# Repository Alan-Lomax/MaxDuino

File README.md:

# MaxDuino
Is a small PCB carrier board that acts as a host for an Arduino NANO.
The PCB provides a multitude of supporting features for the NANO.
It is targeted for use as a model railway animation tool (see feature list)
Because of its flexibility it can be used in many different scenarios.

<B>There are two current versions according to needs:</B>
<Li>R1.6 uses RJ-45 jacks (network patch cords) for power and communications
<Li>R1.4 uses screw terminals for simple wire connections

## Key Features
<Li>Arduino Nano R3 is fully utilized.
<Li>On board NeoPixel for flexible diagnostic use and status reporting.
<Li>Robust on board DC power supply (5V DC, 9-15V DC/AC, or DCC)
<Li>DFRobot MP3 player with SD card and speaker terminals
<Li>Lots of 3 pin headers and an I2C header
<Li>Opto Isolator for decoding DCC packets
<Li>A RJ45 jack is used to connect 12VDC power and RS485 signals between R1.6 boards
<li>Two sets of jacks are provided for easy daisy chaining
<Li>The MAX485 chip has seperate DE/RE pins allowing ICSP of the Arduino. 
<Li>Sample sketches for testing, and to accelerate your own development.
<Li>Detailed build instructions are provided in Excel.

## Status of MaxDuino development 
### Rev 1.6 Is The Latest RJ45 Version 
<Li>No functionality differences vs R1.5.  Minor improvements are: 
<Li>Improved spacing around votage regulator for heatsink mounting
<Li>Added stencilling around 5 volt terminals indicating polarity
<Li>Brought the preamp pins on the Mp3 player out to pads (some people uae external amps)

Since the R1.4 version
<Li>The previous screw terminals for RS485 have been replaced with RJ45 jacks.
<Li>The power supply section received a major redesign.
<li>The round bridge diode is replaced with 4 discrete diodes.
<Li>3 additional diodes are used to drop the input voltage into the L7805 regulator
<Li>A diode has been used to prevent backfeeding power onto the network cable 
(Substitute a jumper where feeding power out is the desired behaviour)
<li>Screw terminals for a speaker are deleted. (Now using 2 pin headers)
<Li>Remote power and RS485 coms tested via a standard network patch cable</Li>
<Li><B>The full test suite has been run and all testing passed successfully.</B>

## Known Issues
<Li>None

### Rev 1.4 Is The Latest Version using screw terminals
<Li>This version is electrically the same as Version 1.3) however the 
<Li>silkscreen errors have been addressed</Li>
<Li><B>All functional testing passed successfully.</B></Li>
<Li>Updated test sketches provided. Test code reflects correct pin assignments,
<Li>Sketches are simplified and compartmentalized as to their the test scope.

### Rev 1.3 and Older Have been removed from GitHub (Files are in the archive)

## MaxDuino KiCad files including GERBERS.
The KiCad files are essentially 'source code' and include:
<Li>the schematic and
<Li>the Printed Circuit Board art work
The Kicad software checks for consistency between these two.

The Gerber files can be thought of as the 'compiled version'. The Gerbers
are seperate files, one for each step in the manufacturing process of a PCB.
The Gerbers are normally saved as a ZIP file and the Zip file is what gets
submitted for manufacture at the fabrication facility of your choice.

# The Panel Version
The MaxDuino PCB is sized 50 mm x 100 mm which means it can easily be panelized
in sets of two. This makes the panelized Maxduino fit on a single 100 mm x 100 mm 
PCB which is the normal 'minimum size' for billing. The short version of this 
is you get twice as many MaxDuinos at no extra cost.

There is a seperate folder containing the Panelized version of the Gerbers.

# Be Aware
Normally all EDITS should be done to the 'single PCB' and then it be repanelized
To repanelize you start a new Kicad project (one with no contents)
and run a 'plug in' to panelize things. You will specfiy which other 
file has the PCB layout you want to panelize. You also set the number of
rows (2) and collumns (1)
The only manual step needed is to add a horizontal line on the edge cut layer.
This will be a 'Vee-Cut' and allows separating the two PCBs easily.

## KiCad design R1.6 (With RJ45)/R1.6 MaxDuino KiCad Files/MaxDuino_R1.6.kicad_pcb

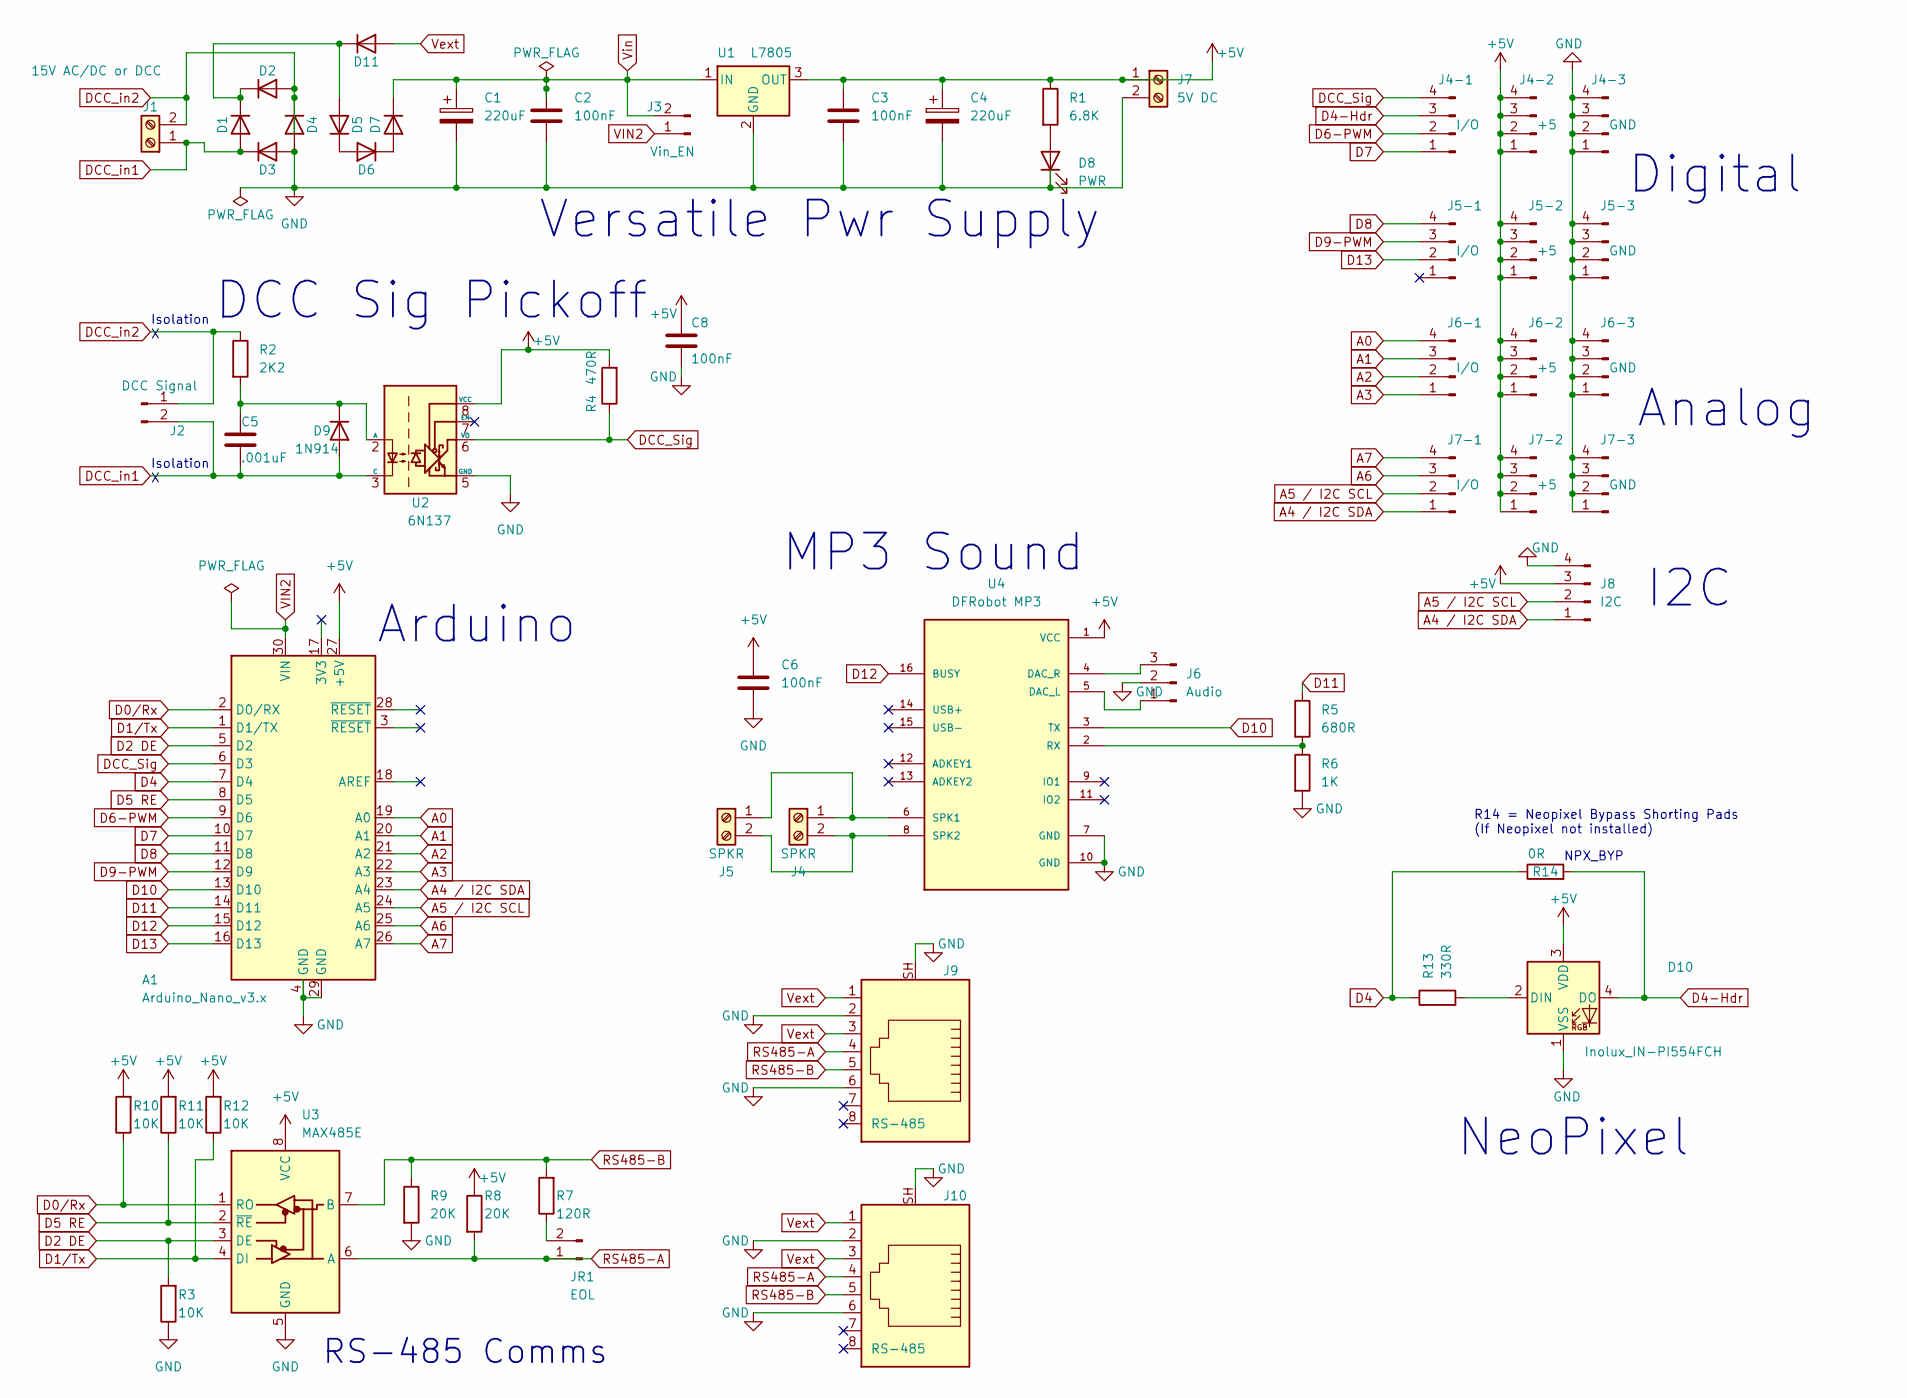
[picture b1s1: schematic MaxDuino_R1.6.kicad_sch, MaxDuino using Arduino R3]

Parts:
A1: Arduino_Nano_v3.x; Arduino_Nano
C1, C4: 220uF; CP_Radial_D6.3mm_P2.50mm
C2, C3, C6, C8: 100nF; C_Disc_D7.0mm_W2.5mm_P5.00mm
C5: .001uF; C_Disc_D7.0mm_W2.5mm_P5.00mm
D1, D2, D3, D4, D5, D6, D7, D11: 1N4001; D_DO-41_SOD81_P10.16mm_Horizontal
D8: PWR; LED_D5.0mm
D9: 1N914; D_DO-35_SOD27_P7.62mm_Horizontal
D10: Inolux_IN-PI554FCH; LED_Inolux_IN-PI554FCH_PLCC4_5.0x5.0mm_P3.2mm
J1: 15V AC/DC or DCC; TerminalBlock_Phoenix_MKDS-3-2-5.08_1x02_P5.08mm_Horizontal
J2: DCC Signal; PinHeader_1x02_P2.54mm_Horizontal
J3: Vin_EN; PinHeader_1x02_P2.54mm_Vertical
J4, J5: SPKR; PinHeader_1x02_P2.54mm_Vertical
J4-1, J5-1, J6-1, J7-1: I/O; PinHeader_1x04_P2.54mm_Vertical
J4-2, J5-2, J6-2, J7-2: +5; PinHeader_1x04_P2.54mm_Vertical
J4-3, J5-3, J6-3, J7-3: GND; PinHeader_1x04_P2.54mm_Vertical
J6: Audio; PinHeader_1x03_P2.54mm_Vertical
J7: 5V DC; TerminalBlock_Phoenix_MKDS-3-2-5.08_1x02_P5.08mm_Horizontal
J8: I2C; PinHeader_1x04_P2.54mm_Vertical
J9, J10: RS-485; RJ45_Ninigi_GE
JR1: EOL; PinHeader_1x02_P2.54mm_Vertical
R1: 6.8K; R_Axial_DIN0207_L6.3mm_D2.5mm_P7.62mm_Horizontal
R2: 2K2; R_Axial_DIN0207_L6.3mm_D2.5mm_P7.62mm_Horizontal
R3, R10, R11, R12: 10K; R_Axial_DIN0207_L6.3mm_D2.5mm_P7.62mm_Horizontal
R4: 470R; R_Axial_DIN0207_L6.3mm_D2.5mm_P7.62mm_Horizontal
R5: 680R; R_Axial_DIN0207_L6.3mm_D2.5mm_P7.62mm_Horizontal
R6: 1K; R_Axial_DIN0207_L6.3mm_D2.5mm_P7.62mm_Horizontal
R7: 120R; R_Axial_DIN0207_L6.3mm_D2.5mm_P7.62mm_Horizontal
R8, R9: 20K; R_Axial_DIN0207_L6.3mm_D2.5mm_P7.62mm_Horizontal
R13: 330R; R_Axial_DIN0207_L6.3mm_D2.5mm_P7.62mm_Horizontal
R14: 0R; R_0805_2012Metric
U1: L7805; TO-220-3_Vertical
U2: 6N137; DIP-8_W7.62mm
U3: MAX485E; DIP-8_W7.62mm
U4: DFRobot MP3; MODULE_DFR0299

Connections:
+5V: A1.27 (+5V), C3.1, C4.1, C6.1, C8.1, D10.3 (VDD), J4-2.1, J4-2.2, J4-2.3, J4-2.4, J5-2.1, J5-2.2, J5-2.3, J5-2.4, J6-2.1, J6-2.2, J6-2.3, J6-2.4, J7.1, J7-2.1, J7-2.2, J7-2.3, J7-2.4, J8.3, R1.1, R4.2, R8.1, R10.2, R11.2, R12.2, U1.3 (OUT), U2.8 (VCC), U3.8 (VCC), U4.1 (VCC)
A0: A1.19 (A0), J6-1.4
A1: A1.20 (A1), J6-1.3
A2: A1.21 (A2), J6-1.2
A3: A1.22 (A3), J6-1.1
A4 / I2C SDA: A1.23 (A4), J7-1.1, J8.1
A5 / I2C SCL: A1.24 (A5), J7-1.2, J8.2
A6: A1.25 (A6), J7-1.3
A7: A1.26 (A7), J7-1.4
D0/Rx: A1.2 (D0/RX), R10.1, U3.1 (RO)
D1/Tx: A1.1 (D1/TX), R12.1, U3.4 (DI)
D2 DE: A1.5 (D2), R3.2, U3.3 (DE)
D4: A1.7 (D4), R13.1, R14.1
D4-Hdr: D10.4 (DO), J4-1.3, R14.2
D5 RE: A1.8 (D5), R11.1, U3.2 (~RE)
D6-PWM: A1.9 (D6), J4-1.2
D7: A1.10 (D7), J4-1.1
D8: A1.11 (D8), J5-1.4
D9-PWM: A1.12 (D9), J5-1.3
D10: A1.13 (D10), U4.3 (TX)
D11: A1.14 (D11), R5.1
D12: A1.15 (D12), U4.16 (BUSY)
D13: A1.16 (D13), J5-1.2
DCC_Sig: A1.6 (D3), J4-1.4, R4.1, U2.6 (VO)
DCC_in1: C5.2, D1.2 (A), D3.1 (K), D9.2 (A), J1.1, J2.2, U2.3 (C)
DCC_in2: D2.2 (A), D4.1 (K), J1.2, J2.1, R2.1
GND: A1.4 (GND), A1.29 (GND), C1.2, C2.2, C3.2, C4.2, C6.2, C8.2, D3.2 (A), D4.2 (A), D8.1 (K), D10.1 (VSS), J4-3.1, J4-3.2, J4-3.3, J4-3.4, J5-3.1, J5-3.2, J5-3.3, J5-3.4, J6.2, J6-3.1, J6-3.2, J6-3.3, J6-3.4, J7.2, J7-3.1, J7-3.2, J7-3.3, J7-3.4, J8.4, J9.2, J9.6, J9.SH, J10.2, J10.6, J10.SH, R3.1, R6.2, R9.2, U1.2 (GND), U2.5 (GND), U3.5 (GND), U4.7 (GND), U4.10 (GND)
unnamed: D1.1 (K), D2.1 (K), D5.2 (A), D11.1 (K)
unnamed: D5.1 (K), D6.2 (A)
unnamed: D6.1 (K), D7.2 (A)
unnamed: D8.2 (A), R1.2
unnamed: C5.1, D9.1 (K), R2.2, U2.2 (A)
unnamed: D10.2 (DIN), R13.2
unnamed: J4.1, J5.1, U4.6 (SPK1)
unnamed: J4.2, J5.2, U4.8 (SPK2)
unnamed: J6.1, U4.5 (DAC_L)
unnamed: J6.3, U4.4 (DAC_R)
unnamed: JR1.2, R7.1
unnamed: R5.2, R6.1, U4.2 (RX)
RS485-A: J9.4, J10.4, JR1.1, R8.2, U3.6 (A)
RS485-B: J9.5, J10.5, R7.2, R9.1, U3.7 (B)
VIN2: A1.30 (VIN), J3.1
Vext: D11.2 (A), J9.1, J9.3, J10.1, J10.3
Vin: C1.1, C2.1, D7.1 (K), J3.2, U1.1 (IN)

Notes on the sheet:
RS-485 Comms
MP3 Sound
Digital
I2C
NeoPixel
DCC Sig Pickoff
NPX_BYP
R14 = Neopixel Bypass Shorting Pads (If Neopixel not installed)
Versatile Pwr Supply
Isolation X
Analog
Arduino

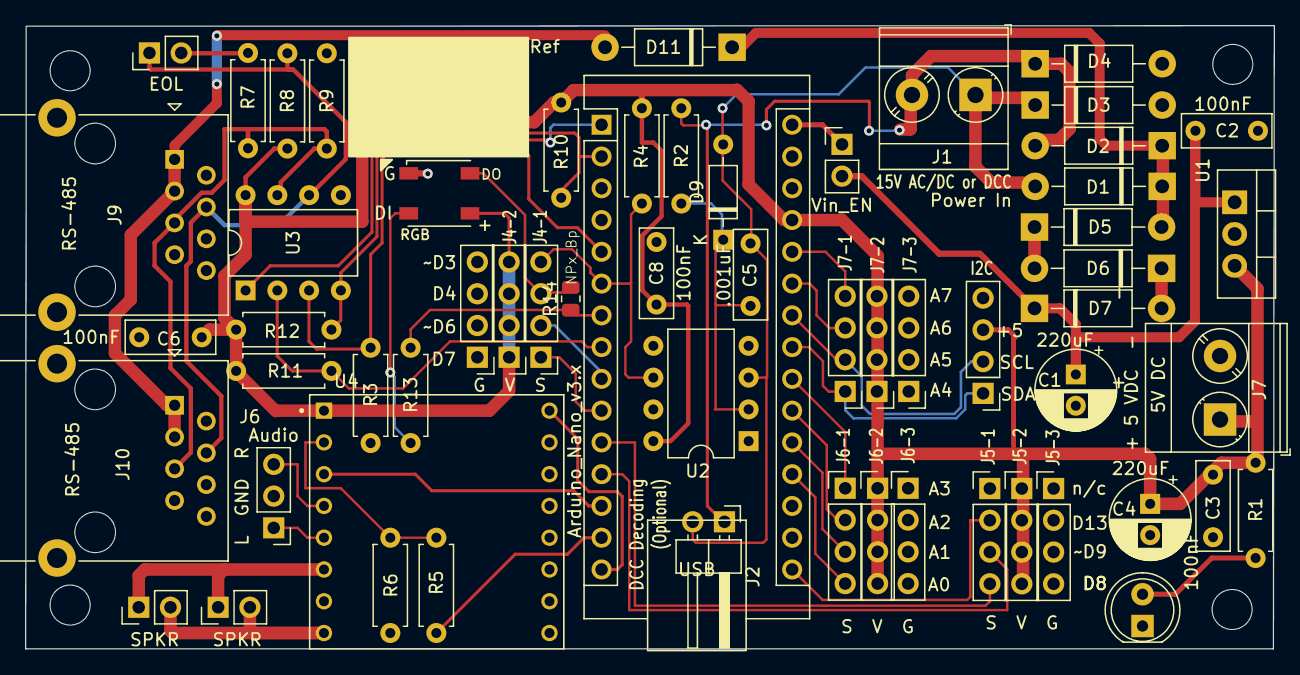
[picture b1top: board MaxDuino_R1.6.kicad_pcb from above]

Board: 2 copper layers, 99.8 x 49.8 mm, 65 parts (1 on the bottom side), 44 nets.

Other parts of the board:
M3.1, M3.2, M3.3, M3.4: M3; MountingHole_3.2mm_M3
MERG: LOGO; MERG_LOGO

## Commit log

2023-07-01 Initial Upload at v1.1
    For MERG Article
2023-07-01 Update README.md
    Expanded and clarified
2023-07-01 Update README.md
    Minor Edit
2023-07-01 Update readme.txt
    Minor Edit
2023-07-01 Updated Article to Final
    Now Ready for Submission
2023-07-15 Improved Documentation
    With R1.1 on hand took opportunity to revise build instructions and add polish to sketches for the the test cases.
2023-08-09 Block diagram added
2023-08-09 Moved documentation into its own distinct folder.
    Documentation was previously buried in SD-Card contents. This did not make sense if the end user had no intention of including MP3 player capability. Hopefully easier to find and follow now.
2023-08-19 Create MaxDuino Development Roadmap.xlsx
    Main Planning document showing proposed developments for the MaxDuino platform and timing of same.
2023-09-08 Rev 1.2
    Minor Improvements to RS485 circuit and NeoPixel circuit.
    Revisited documentation. Test code for RS485 will need updating (when I have the PCB's in hand)
2023-09-28 Made both R1.1 and R1.2 available
    Slight differences in what works or does not work.
    Recommended: R1.1 as all features work but only uses a single pin for RS485 direction control.
2023-10-15 Updated for R1.4 (and R1.3)
    MERG Journal article submitted was based on R1.3 (All testing passed, plus improvement suggestions from R1.1 all incorporated).
    In the editing and proofing process some PCB stencil errors were noted on the R1.3 PCB - version 1.4 fixes these minor issues.
    Electrically R1.3 and R1.4 are the same.
2023-10-15 Update README.md
    Revised for R1.4. Final Testing all Passed.
2023-10-15 Update README.md
    Rev 1.4
2023-10-15 Updated Roadmap Post R1.4
2023-10-27 Update MaxDuino_Assembly_Instructions R1.4.xlsm
    Minor update
2023-11-30 Ver 1.5 plus Reorg files
    With V1.5 being pushed out I decided to organize files by version number. Thus all files associated with a given version are in one folder. This is cleaner and makes finding relevant files easy. Obso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
2023-12-02 Update README.md
    Clarification of Text
2023-12-21 Updated to R1.6
    Minor updates to PCB
2024-01-10 Updated Design Walkthrough
    Minor update - MP3 player has preamp pins now.
2024-06-15 Documentation Improvements
    Improved documentation, added photos.
